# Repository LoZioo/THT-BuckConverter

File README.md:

# THT-BuckConverter
A small PCB of a DC-DC Buck-Converter based on the famous LM2596 IC entirely built with just THT components!

## PCB 3D front render

## PCB 3D back render

## Schematics

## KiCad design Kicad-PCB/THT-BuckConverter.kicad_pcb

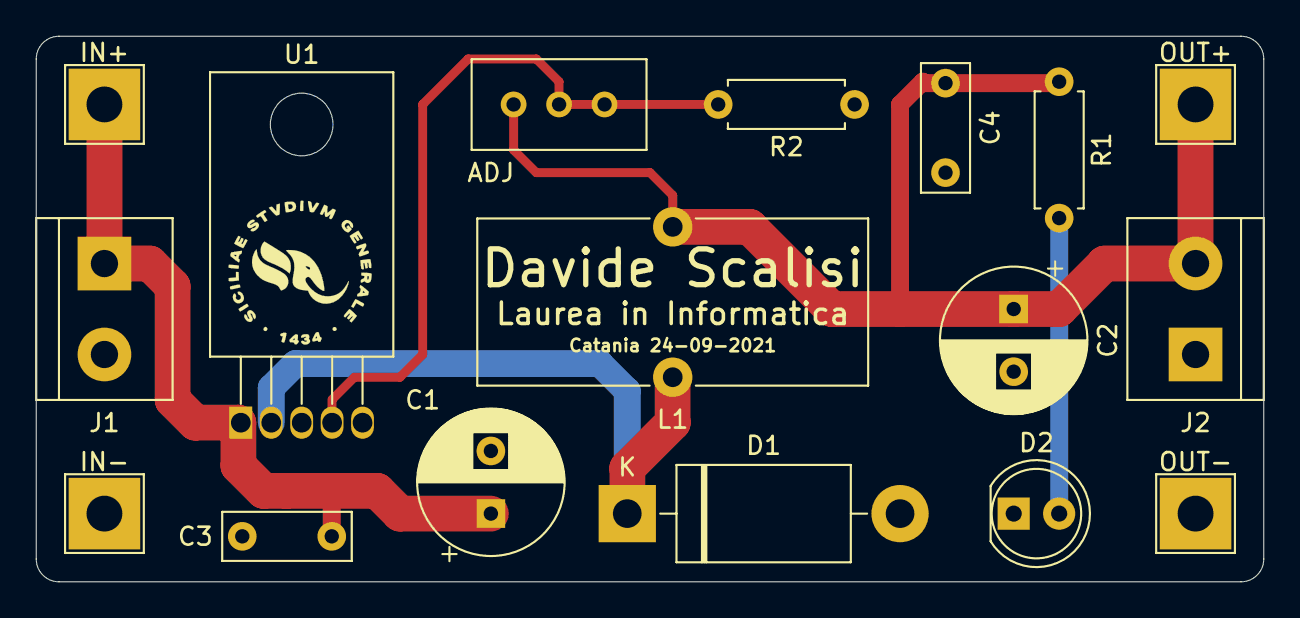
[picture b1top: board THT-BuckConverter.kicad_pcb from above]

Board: 2 copper layers, 68.6 x 30.5 mm, 17 parts (0 on the bottom side), 6 nets.

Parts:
ADJ: 10K; Potentiometer_Bourns_3296W_Vertical
C1: 100uF 50V; CP_Radial_D8.0mm_P3.50mm
C2: 220uF 35V; CP_Radial_D8.0mm_P3.50mm
C3, C4: .1uF; C_Rect_L7.0mm_W2.5mm_P5.00mm
D1: 1N5822; D_DO-201AD_P15.24mm_Horizontal
D2: LED; LED_D5.0mm
IN+: IN; TestPoint_THTPad_4.0x4.0mm_Drill2.0mm
IN-: GND; TestPoint_THTPad_4.0x4.0mm_Drill2.0mm
J1: IN; TerminalBlock_bornier-2_P5.08mm
J2: OUT; TerminalBlock_bornier-2_P5.08mm
L1: 47uH; L_Toroid_Vertical_L21.6mm_W9.1mm_P8.40mm_Bourns_5700
OUT+: OUT; TestPoint_THTPad_4.0x4.0mm_Drill2.0mm
OUT-: GND; TestPoint_THTPad_4.0x4.0mm_Drill2.0mm
R1: 1K; R_Axial_DIN0207_L6.3mm_D2.5mm_P7.62mm_Horizontal
R2: 330R; R_Axial_DIN0207_L6.3mm_D2.5mm_P7.62mm_Horizontal
U1: LM2596S-ADJ; TO-220-5_Horizontal_TabDown

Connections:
GND: C1.2, C2.2, C3.2, C4.2, D1.2, D2.1, IN-.1, J1.2, J2.1, OUT-.1, R2.1, U1.3, U1.5
IN: C1.1, C3.1, IN+.1, J1.1, U1.1
unnamed: D1.1, L1.1, U1.2
unnamed: D2.2, R1.2
unnamed: ADJ.1, ADJ.2, R2.2, U1.4
OUT: ADJ.3, C2.1, C4.1, J2.2, L1.2, OUT+.1, R1.1

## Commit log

2022-03-30 feat: release 1.0.0
2022-04-01 feat: added screenshoots
